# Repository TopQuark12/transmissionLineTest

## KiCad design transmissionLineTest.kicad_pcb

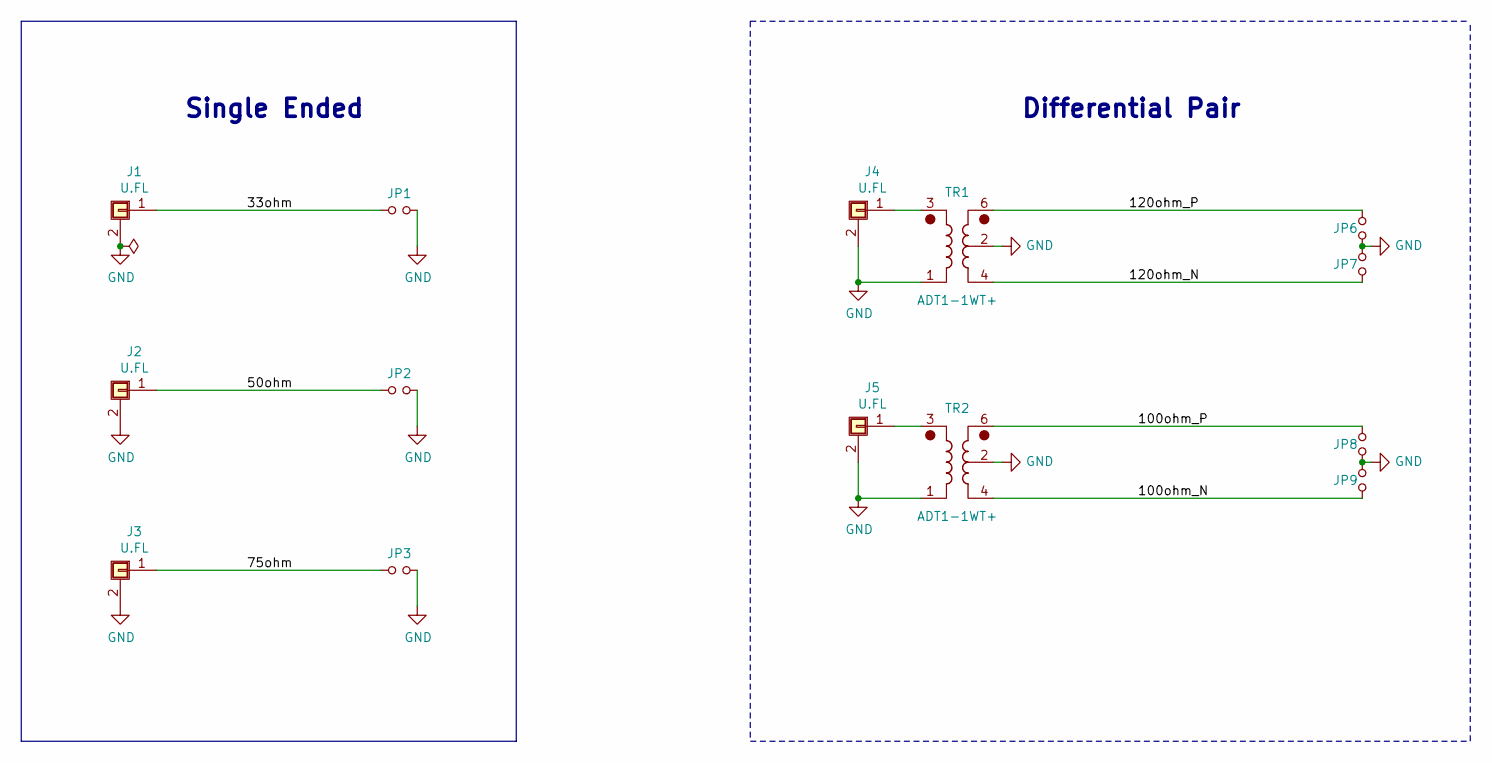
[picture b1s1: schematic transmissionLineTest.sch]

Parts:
J1, J2, J3, J4, J5: U.FL; U.FL_Hirose_U.FL-R-SMT-1_Vertical
JP1, JP2, JP3, JP6, JP7, JP8, JP9: Jumper_NO_Small; SolderJumper-2_P1.3mm_Open_RoundedPad1.0x1.5mm
TR1, TR2: ADT1-1WT+; Mini-Circuits_CD542_H2.84mm

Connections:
/33ohm: J1.1, JP1.1
/50ohm: J2.1, JP2.1
/75ohm: J3.1, JP3.1
/100ohm_N: JP9.1, TR2.4
/100ohm_P: JP8.2, TR2.6
/120ohm_N: JP7.1, TR1.4
/120ohm_P: JP6.2, TR1.6
GND: J1.2 (Shield), J2.2 (Shield), J3.2 (Shield), J4.2 (Shield), J5.2 (Shield), JP1.2, JP2.2, JP3.2, JP6.1, JP7.2, JP8.1, JP9.2, TR1.1, TR1.2, TR2.1, TR2.2
unnamed: J4.1, TR1.3
unnamed: J5.1, TR2.3

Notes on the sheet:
Single Ended
Differential Pair

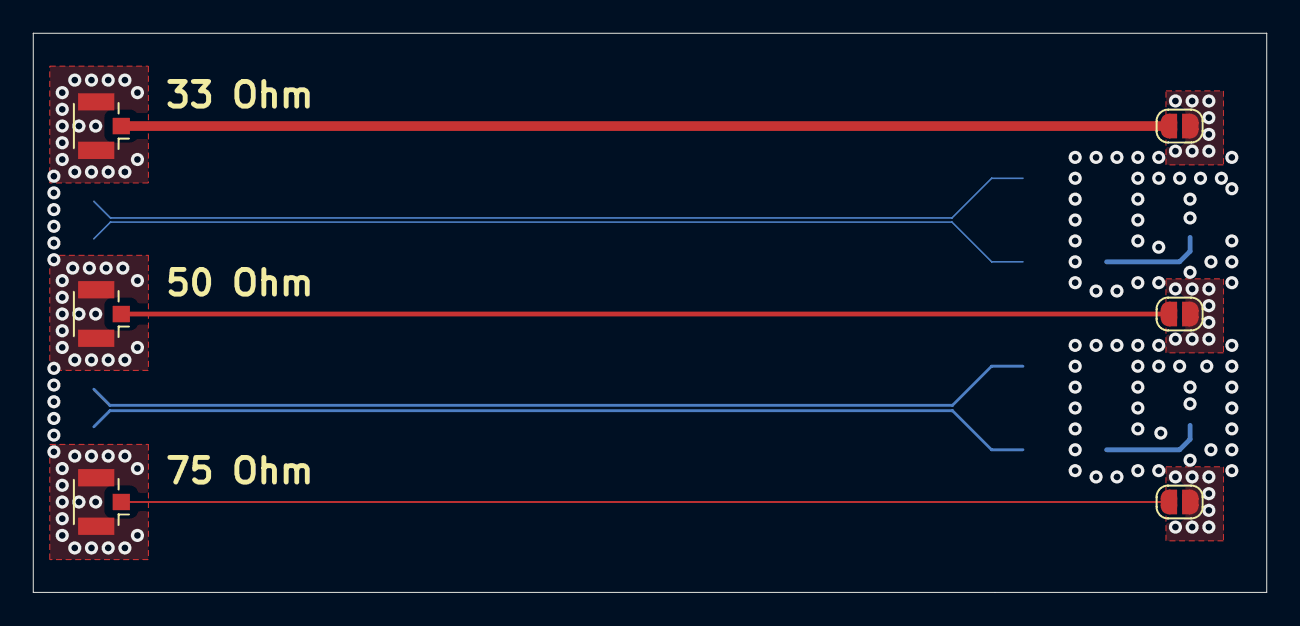
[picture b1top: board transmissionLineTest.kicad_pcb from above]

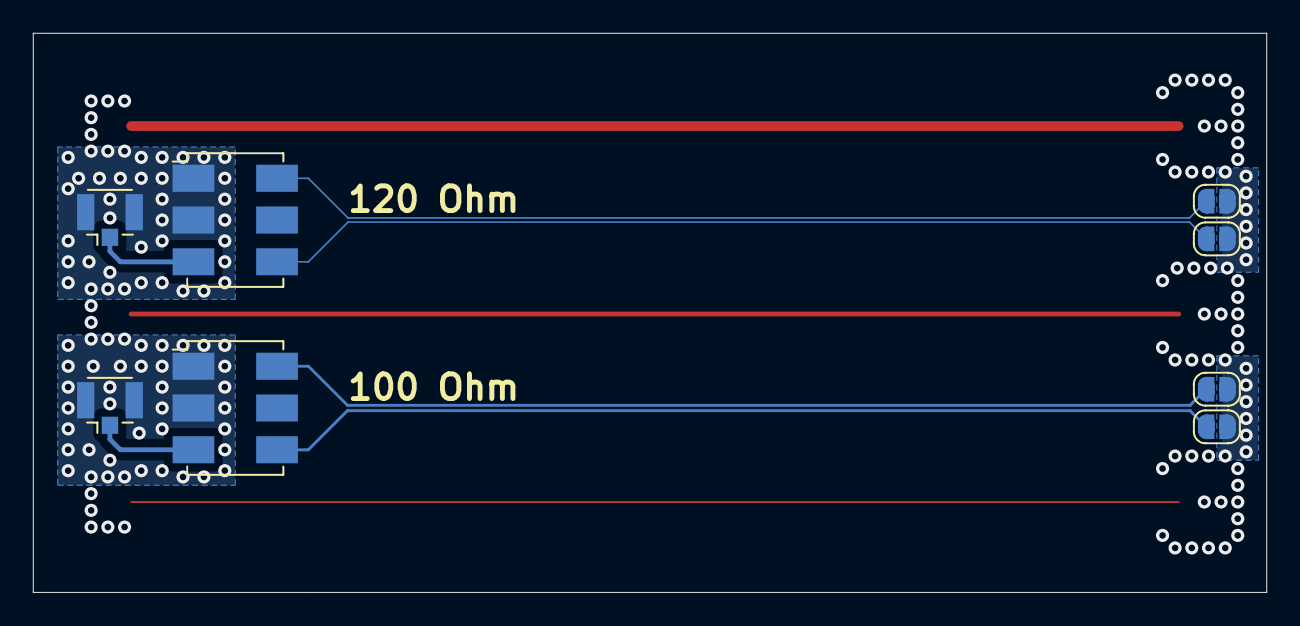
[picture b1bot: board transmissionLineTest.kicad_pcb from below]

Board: 4 copper layers, 75.0 x 34.0 mm, 14 parts (8 on the bottom side), 10 nets.

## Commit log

2021-03-03 create project
2021-03-03 single ended test traces
2021-03-03 cleanup
2021-03-04 add diff test
2021-03-04 update schematics
